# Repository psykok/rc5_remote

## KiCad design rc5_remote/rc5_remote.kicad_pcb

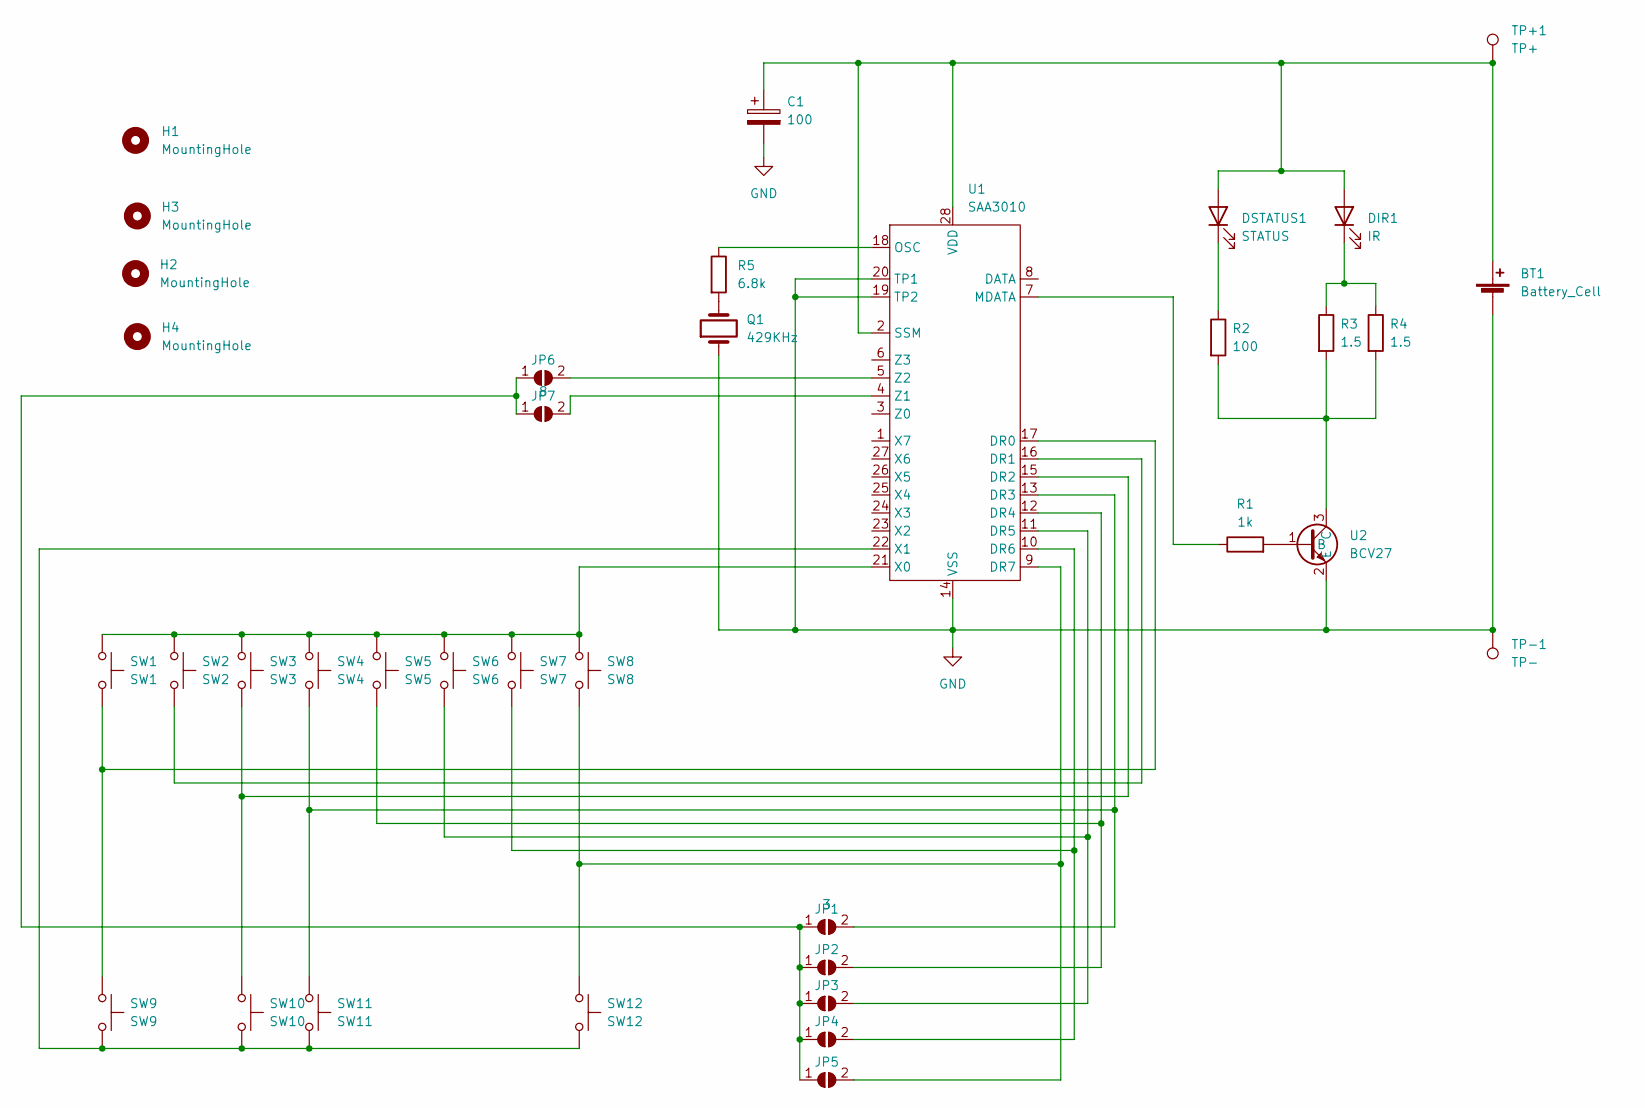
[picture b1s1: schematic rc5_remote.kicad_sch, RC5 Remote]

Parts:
BT1: Battery_Cell; BatteryHolder_Keystone_1060_1x2032
C1: 100; CP_EIA-3528-12_Kemet-T
DIR1: IR; LED_D5.0mm_Horizontal_O1.27mm_Z3.0mm_IRBlack
DSTATUS1: STATUS; LED_D3.0mm
H1, H2, H3, H4: MountingHole; MountingHole_3mm
JP1: 3; SolderJumper-2_P1.3mm_Bridged_RoundedPad1.0x1.5mm
JP2: 4; SolderJumper-2_P1.3mm_Bridged_RoundedPad1.0x1.5mm
JP3: 5; SolderJumper-2_P1.3mm_Bridged_RoundedPad1.0x1.5mm
JP4: 6; SolderJumper-2_P1.3mm_Bridged_RoundedPad1.0x1.5mm
JP5: 7; SolderJumper-2_P1.3mm_Bridged_RoundedPad1.0x1.5mm
JP6: 16; SolderJumper-2_P1.3mm_Bridged_RoundedPad1.0x1.5mm
JP7: 8; SolderJumper-2_P1.3mm_Bridged_RoundedPad1.0x1.5mm
Q1: 429KHz; CSBF
R1: 1k; R_1206_3216Metric
R2: 100; R_1206_3216Metric
R3, R4: 1.5; R_1206_3216Metric
R5: 6.8k; R_1206_3216Metric
SW1: SW1; SW_SPST_B3S-1000
SW2: SW2; SW_SPST_B3S-1000
SW3: SW3; SW_SPST_B3S-1000
SW4: SW4; SW_SPST_B3S-1000
SW5: SW5; SW_SPST_B3S-1000
SW6: SW6; SW_SPST_B3S-1000
SW7: SW7; SW_SPST_B3S-1000
SW8: SW8; SW_SPST_B3S-1000
SW9: SW9; SW_SPST_B3S-1000
SW10: SW10; SW_SPST_B3S-1000
SW11: SW11; SW_SPST_B3S-1000
SW12: SW12; SW_SPST_B3S-1000
TP+1: TP+; TestPoint_THTPad_D2.5mm_Drill1.2mm
TP-1: TP-; TestPoint_THTPad_D2.5mm_Drill1.2mm
U1: SAA3010; SOIC-28W_7.5x17.9mm_P1.27mm
U2: BCV27; SOT-23

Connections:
GND: BT1.2 (-), C1.2, Q1.1, TP-1.1, U1.14 (VSS), U1.19 (TP2), U1.20 (TP1), U2.2 (E)
unnamed: BT1.1 (+), C1.1, DIR1.2 (A), DSTATUS1.2 (A), TP+1.1, U1.2 (SSM), U1.28 (VDD)
unnamed: DIR1.1 (K), R3.1, R4.1
unnamed: DSTATUS1.1 (K), R2.1
unnamed: JP1.1 (A), JP2.1 (A), JP3.1 (A), JP4.1 (A), JP5.1 (A), JP6.1 (A), JP7.1 (A)
unnamed: JP1.2 (B), SW4.2, SW11.1, U1.13 (DR3)
unnamed: JP2.2 (B), SW5.2, U1.12 (DR4)
unnamed: JP3.2 (B), SW6.2, U1.11 (DR5)
unnamed: JP4.2 (B), SW7.2, U1.10 (DR6)
unnamed: JP5.2 (B), SW8.2, SW12.1, U1.9 (DR7)
unnamed: JP6.2 (B), U1.5 (Z2)
unnamed: JP7.2 (B), U1.4 (Z1)
unnamed: Q1.2, R5.2
unnamed: R1.1, U1.7 (MDATA)
unnamed: R1.2, U2.1 (B)
unnamed: R2.2, R3.2, R4.2, U2.3 (C)
unnamed: R5.1, U1.18 (OSC)
unnamed: SW1.1, SW2.1, SW3.1, SW4.1, SW5.1, SW6.1, SW7.1, SW8.1, U1.21 (X0)
unnamed: SW1.2, SW9.1, U1.17 (DR0)
unnamed: SW2.2, U1.16 (DR1)
unnamed: SW3.2, SW10.1, U1.15 (DR2)
unnamed: SW9.2, SW10.2, SW11.2, SW12.2, U1.22 (X1)

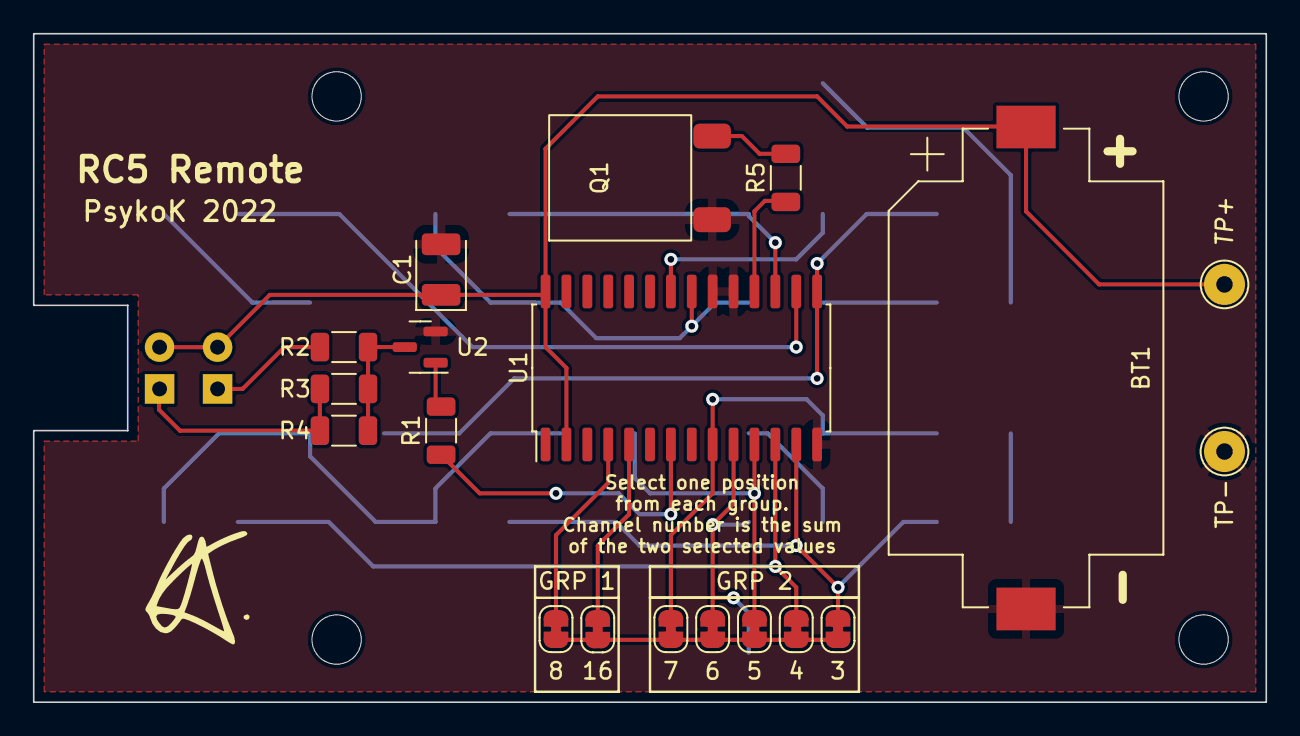
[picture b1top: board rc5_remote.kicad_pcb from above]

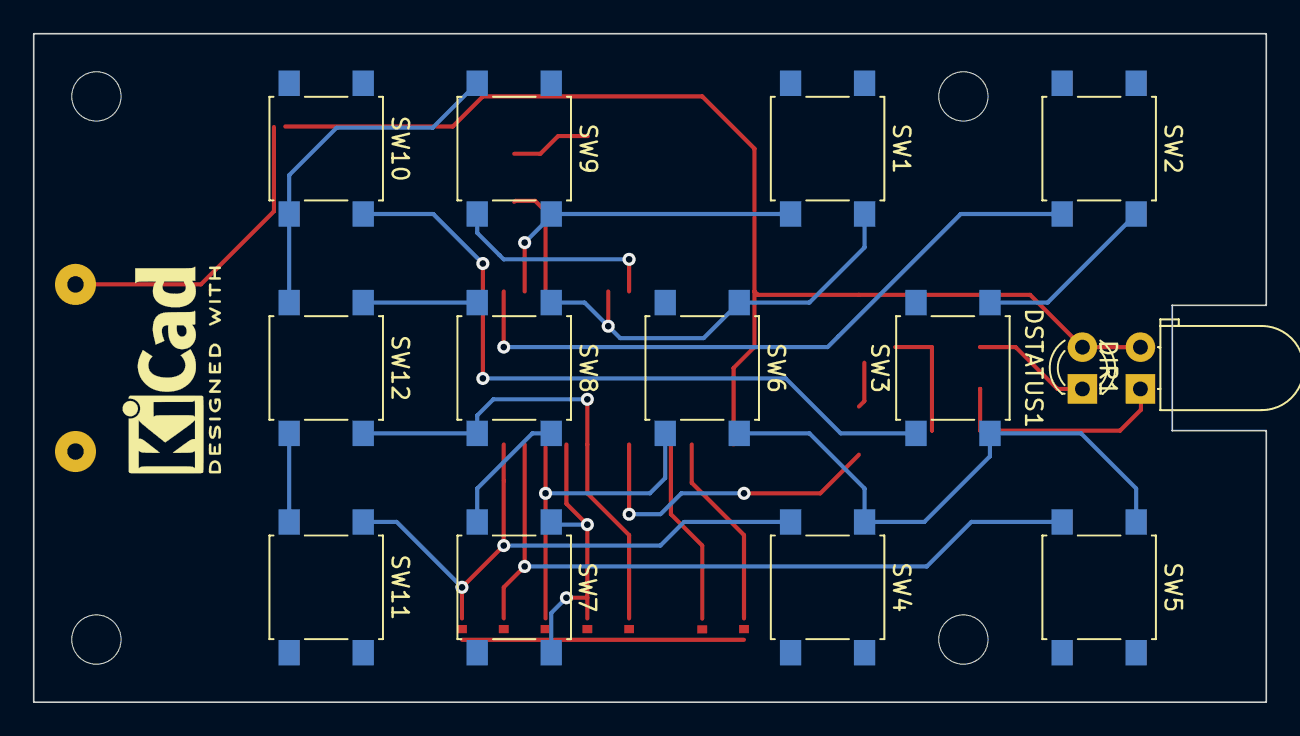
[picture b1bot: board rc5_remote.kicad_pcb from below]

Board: 2 copper layers, 74.9 x 40.6 mm, 37 parts (14 on the bottom side), 22 nets.

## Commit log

2023-06-02 first release
